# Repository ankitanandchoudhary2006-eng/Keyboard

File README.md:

# Keyboard

I made a custom 60% layout keyboard which has per swich diode for ghosting protection and it has hotswaps So that we can change the switches anytime as per our wich . The MCU is based on STM32F072CBT6 and we have designed the circuit using  a custom chip to save space (instread of a module). PCB was designed in Kicad and CAD was made in Fusion.

### Features
- Based on STM32F072CBT6 Chip
- Has 60% Compact layout
- uses diodes for ghosting prevention

# BOM - Bill of Materials

## Components

| Component | Qty | Total Price (USD) | Purchase Link |
|---|---:|---:|---|
| 4.7uF Capacitor | 2 | $0.226 | [JLCPCB](https://jlcpcb.com/partdetail/24469-CL05A475MP5NRNC/C23733) |
| 100nF Capacitor | 4 | $0.0552 | [JLCPCB](https://jlcpcb.com/partdetail/1877-CL05B104KO5NNNC/C1525) |
| 1uF Capacitor | 4 | $0.110 | [JLCPCB](https://jlcpcb.com/partdetail/53938-CL05A105KA5NQNC/C52923) |
| 10uF Capacitor | 1 | $0.394 | [JLCPCB](https://jlcpcb.com/partdetail/16204-CL05A106MQ5NUNC/C15525) |
| PRTR5V0U2X | 1 | $0.3762 | [JLCPCB](https://jlcpcb.com/partdetail/TECHPUBLIC-PRTR5V0U2X/C2827688) |
| 1N4148W Diode | 60 | $1.6616 | [JLCPCB](https://jlcpcb.com/partdetail/ST_Semtech-1N4148W/C81598) |
| 500mA Fuse | 1 | $0.2538 | [JLCPCB](https://jlcpcb.com/partdetail/TECHFUSE-nSMD050/C69688) |
| 2N7002 MOSFET | 1 | $0.158 | [JLCPCB](https://jlcpcb.com/partdetail/9040-2N7002/C8545) |
| 5.1k Resistor | 2 | $0.028 | [JLCPCB](https://jlcpcb.com/partdetail/26648-0402WGF5101TCE/C25905) |
| 33k Resistor | 1 | $0.038 | [JLCPCB](https://jlcpcb.com/partdetail/26522-0402WGF3302TCE/C25779) |
| 10k Resistor | 1 | $0.030 | [JLCPCB](https://jlcpcb.com/partdetail/26487-0402WGF1002TCE/C25744) |
| 100k Resistor | 1 | $0.018 | [JLCPCB](https://jlcpcb.com/partdetail/26484-0402WGF1003TCE/C25741) |
| Tactile Switch | 1 | $0.215 | [JLCPCB](https://jlcpcb.com/partdetail/XKBConnection-TS_1187A_B_AB/C318884) |
| XC6206P332MR | 1 | $0.690 | [JLCPCB](https://jlcpcb.com/partdetail/TorexSemicon-XC6206P332MRG/C5446) |
| STM32F072CBT6 | 1 | $5.518 | [JLCPCB](https://jlcpcb.com/partdetail/STMicroelectronics-STM32F072C8T6/C80488) |
| USB Type-C Connector | 1 | $0.3738 | [JLCPCB](https://jlcpcb.com/partdetail/Korean_HropartsElec-TYPE_C_31_M12/C165948) |
| HOTSWAP Socket | 61 | $0.00 (Already Have) | [Meckeys](https://meckeys.com/shop/accessories/keyboard-accessories/key-switches/kailh-hot-swap-socket/?attribute_pa_variations=white) |
|Stabalizers |1|0|https://meckeys.com/shop/accessories/keyboard-accessories/more/glorious-goat-stabilizers/|

## Manufacturing Cost

| Item | Price (USD) |
|---|---:|
| PCB Engineering Fee | $4.00 |
| PCB Board | $14.70 |
| Via Covering | $0.00 |
| **PCB Total** | **$18.70** |
| PCBA Setup Fee | $25.75 |
| Stencil | $8.27 |
| Components | $10.15 |
| Feeder Loading Fee | $24.80 |
| SMT Assembly | $1.43 |
| Packaging Fee | $0.51 |
| **PCBA Total** | **$70.91** |

## Additional Costs

| Item | Price (USD) |
|---|---:|
| 3D Printing | $11.29 |
| Shipping | $18.24 |

## Final Project Cost

| Category | Price (USD) |
|---|---:|
| PCB Fabrication | $18.70 |
| PCBA Assembly | $70.91 |
| 3D Printing | $11.29 |
| Shipping | $18.24 |
| **Grand Total** | **$119.14** |

**Total Project Cost: $119.14 USD**

## Schematics

## PCB

## CAD

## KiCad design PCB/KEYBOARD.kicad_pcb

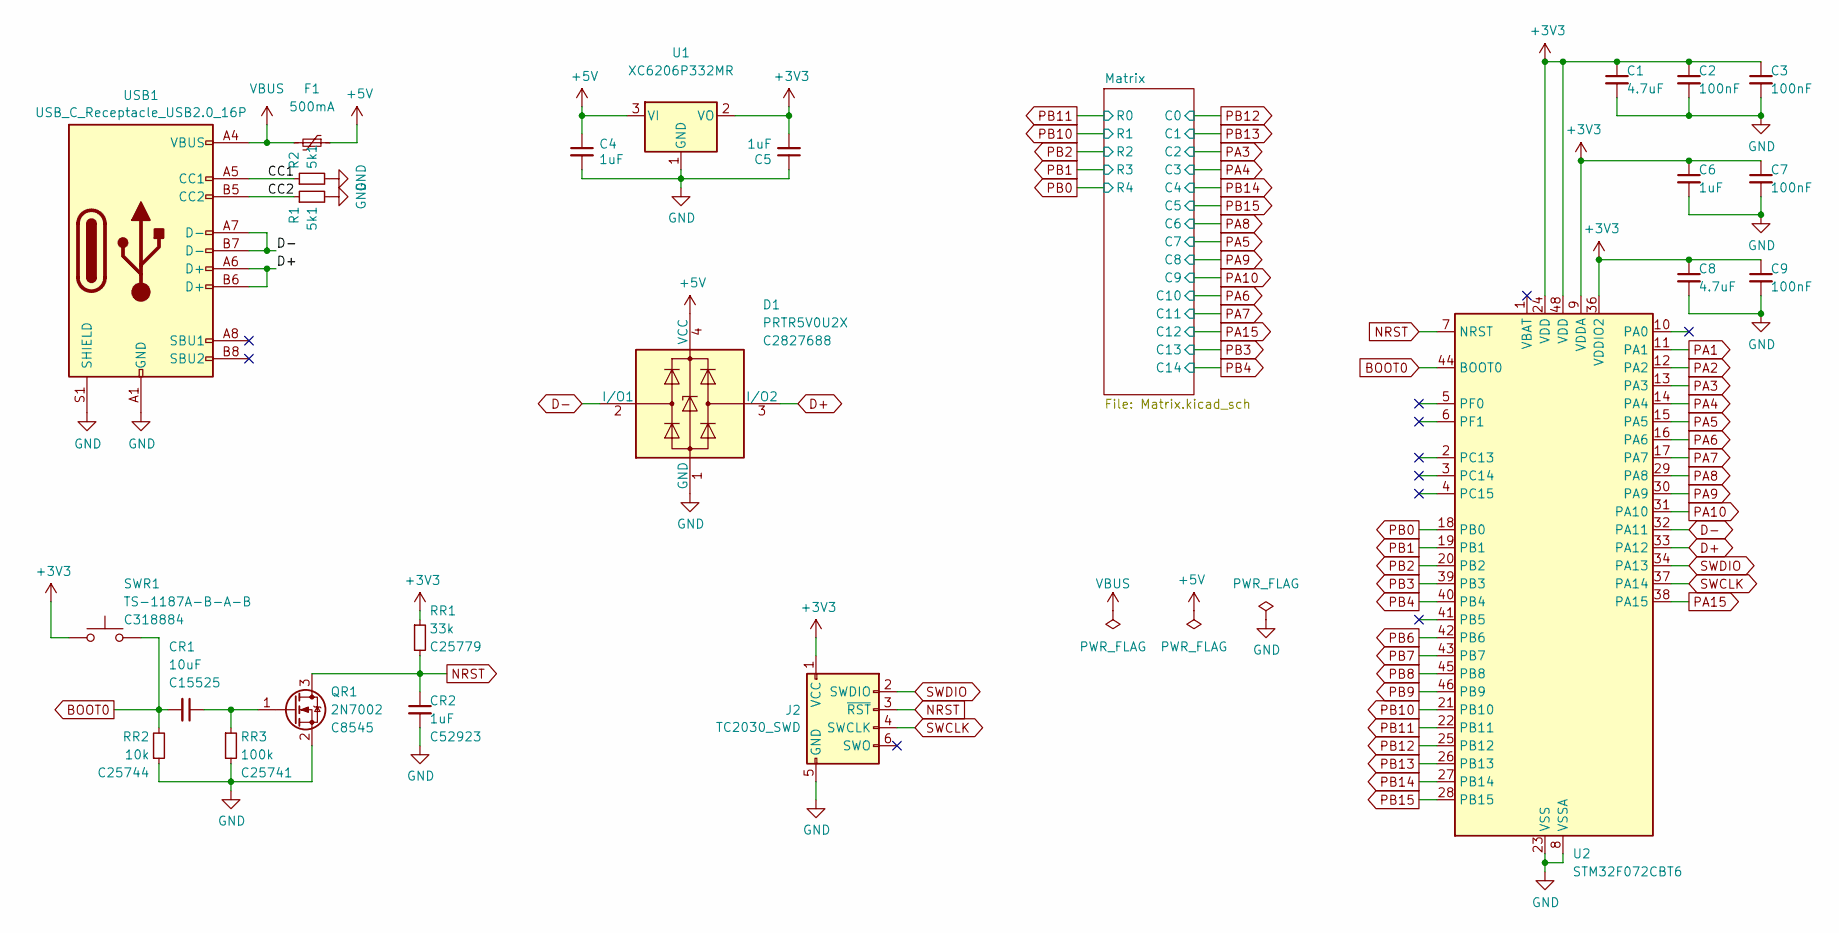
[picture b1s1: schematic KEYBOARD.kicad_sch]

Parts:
C1, C8: 4.7uF; C_0402_1005Metric; MPN CL05A475MP5NRNC; LCSC C23733
C2, C3, C7, C9: 100nF; C_0402_1005Metric; MPN CL05B104KO5NNNC; LCSC C1525
C4, C5, C6: 1uF; C_0402_1005Metric; MPN CL05A105KA5NQNC; LCSC C52923
CR1: 10uF; C_0402_1005Metric; MPN CL05A106MQ5NUNC; LCSC C15525
CR2: 1uF; C_0402_1005Metric; MPN CL05A105KA5NQNC; LCSC C52923
D1: PRTR5V0U2X; SOT-143; MPN PRTR5V0U2X; LCSC C2827688
F1: 500mA; Fuse_1206_3216Metric_Pad1.42x1.75mm_HandSolder; MPN nSMD050; LCSC C69688
J2: TC2030_SWD; CON_TC2030_outlined
QR1: 2N7002; SOT-23; MPN 2N7002; LCSC C8545
R1, R2: 5k1; R_0402_1005Metric; MPN 0402WGF5101TCE; LCSC C25905
RR1: 33k; R_0402_1005Metric; MPN 0402WGF3302TCE; LCSC C25779
RR2: 10k; R_0402_1005Metric; MPN 0402WGF1002TCE; LCSC C25744
RR3: 100k; R_0402_1005Metric; MPN 0402WGF1003TCE; LCSC C25741
SWR1: TS-1187A-B-A-B; SW_SPST_TL3342; MPN TS-1187A-B-A-B; LCSC C318884
U1: XC6206P332MR; SOT-23; MPN XC6206P332MR-G; LCSC C5446
U2: STM32F072CBT6; LQFP-48_7x7mm_P0.5mm; MPN STM32F072CBT6; LCSC C81720
USB1: USB_C_Receptacle_USB2.0_16P; USB_C_Receptacle_HRO_TYPE-C-31-M-12; MPN TYPE-C-31-M-12; LCSC C165948

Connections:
+3V3: C1.1, C2.1, C3.1, C5.2, C6.1, C7.1, C8.1, C9.1, J2.1 (VCC), RR1.1, SWR1.1, U1.2 (VO), U2.9 (VDDA), U2.24 (VDD), U2.36 (VDDIO2), U2.48 (VDD)
+5V: C4.1, D1.4 (VCC), F1.1, U1.3 (VI)
/CC1: R2.1, USB1.A5 (CC1)
/CC2: R1.1, USB1.B5 (CC2)
BOOT0: CR1.2, RR2.2, SWR1.2, U2.44 (BOOT0)
D+: D1.3 (I/O2), U2.33 (PA12), USB1.A6 (D+), USB1.B6 (D+)
D-: D1.2 (I/O1), U2.32 (PA11), USB1.A7 (D-), USB1.B7 (D-)
GND: C1.2, C2.2, C3.2, C4.2, C5.1, C6.2, C7.2, C8.2, C9.2, CR2.2, D1.1 (GND), J2.5 (GND), QR1.2 (S), R1.2, R2.2, RR2.1, RR3.2, U1.1 (GND), U2.8 (VSSA), U2.23 (VSS), U2.35 (VSS), U2.47 (VSS), USB1.A1 (GND), USB1.A12 (GND), USB1.B1 (GND), USB1.B12 (GND), USB1.S1 (SHIELD)
NRST: CR2.1, J2.3 (~RST), QR1.3 (D), RR1.2, U2.7 (NRST)
unnamed: CR1.1, QR1.1 (G), RR3.1
PA1: U2.11 (PA1)
PA2: U2.12 (PA2)
PA3: U2.13 (PA3); also elsewhere on the board
PA4: U2.14 (PA4); also elsewhere on the board
PA5: U2.15 (PA5); also elsewhere on the board
PA6: U2.16 (PA6); also elsewhere on the board
PA7: U2.17 (PA7); also elsewhere on the board
PA8: U2.29 (PA8); also elsewhere on the board
PA9: U2.30 (PA9); also elsewhere on the board
PA10: U2.31 (PA10); also elsewhere on the board
PA15: U2.38 (PA15); also elsewhere on the board
PB0: U2.18 (PB0); also elsewhere on the board
PB1: U2.19 (PB1); also elsewhere on the board
PB2: U2.20 (PB2); also elsewhere on the board
PB3: U2.39 (PB3); also elsewhere on the board
PB4: U2.40 (PB4); also elsewhere on the board
PB6: U2.42 (PB6)
PB7: U2.43 (PB7)
PB8: U2.45 (PB8)
PB9: U2.46 (PB9)
PB10: U2.21 (PB10); also elsewhere on the board
PB11: U2.22 (PB11); also elsewhere on the board
PB12: U2.25 (PB12); also elsewhere on the board
PB13: U2.26 (PB13); also elsewhere on the board
PB14: U2.27 (PB14); also elsewhere on the board
PB15: U2.28 (PB15); also elsewhere on the board
SWCLK: J2.4 (SWCLK), U2.37 (PA14)
SWDIO: J2.2 (SWDIO), U2.34 (PA13)
VBUS: F1.2, USB1.A4 (VBUS), USB1.A9 (VBUS), USB1.B4 (VBUS), USB1.B9 (VBUS)

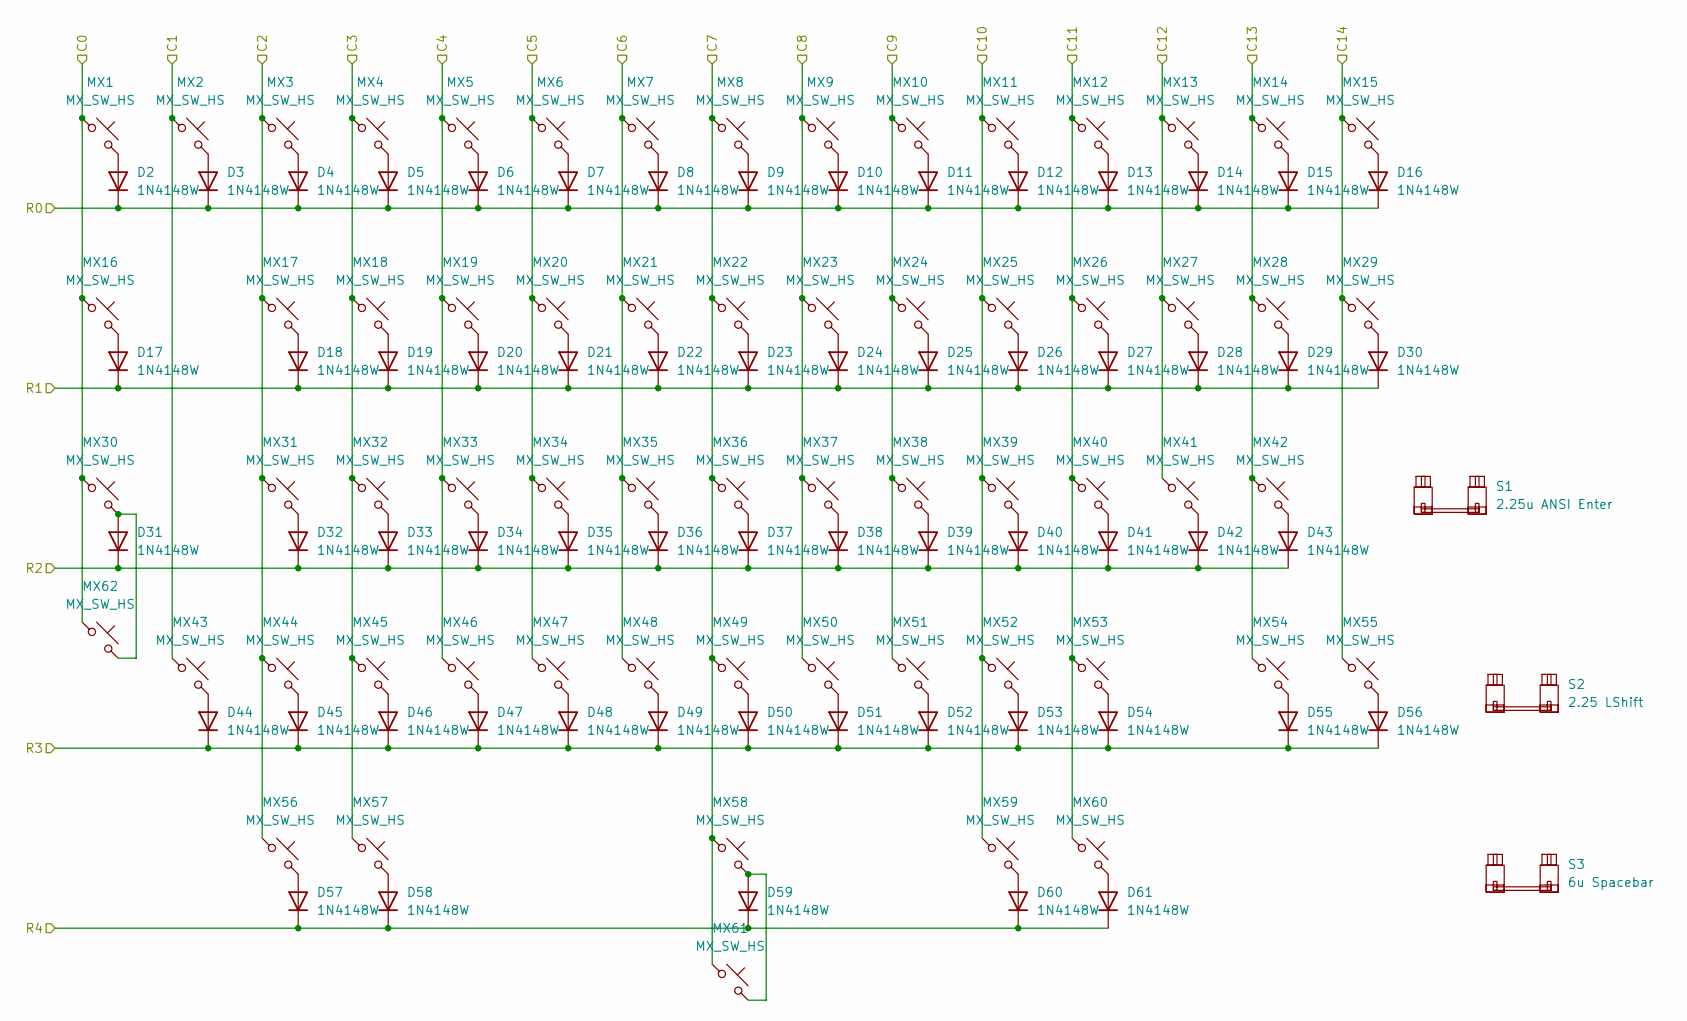
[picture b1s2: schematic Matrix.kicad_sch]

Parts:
D2, D3, D4, D5, D6, D7, D8, D9, D10, D11, D12, D13, D14, D15, D16, D17, D18, D19, D20, D21, D22, D23, D24, D25, D26, D27, D28, D29, D30, D31, D32, D33, D34, D35, D36, D37, D38, D39, D40, D41, D42, D43, D44, D45, D46, D47, D48, D49, D50, D51, D52, D53, D54, D55, D56, D57, D58, D59, D60, D61: 1N4148W; D_SOD-123
MX1, MX2, MX3, MX4, MX5, MX6, MX7, MX8, MX9, MX10, MX11, MX12, MX13, MX14, MX15, MX17, MX18, MX19, MX20, MX21, MX22, MX23, MX24, MX25, MX26, MX27, MX28, MX31, MX32, MX33, MX34, MX35, MX36, MX37, MX38, MX39, MX40, MX41, MX42, MX43, MX44, MX45, MX46, MX47, MX48, MX49, MX50, MX51, MX52, MX53, MX55, MX56, MX58, MX60, MX61: MX_SW_HS; SW_MX_HS_CPG151101S11_1u
MX16, MX29, MX57, MX59: MX_SW_HS; SW_MX_HS_CPG151101S11_1.5u
MX30, MX54: MX_SW_HS; SW_MX_HS_CPG151101S11_1.75u
MX62: MX_SW_HS; SW_MX_HS_CPG151101S11_1.75u_STP_1.25
S1: 2.25u ANSI Enter; STAB_MX_2.25u
S2: 2.25 LShift; STAB_MX_2.25u
S3: 6u Spacebar; STAB_MX_6u_New

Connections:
unnamed: D2.2 (A), MX1.2
unnamed: D3.2 (A), MX2.2
unnamed: D4.2 (A), MX3.2
unnamed: D5.2 (A), MX4.2
unnamed: D6.2 (A), MX5.2
unnamed: D7.2 (A), MX6.2
unnamed: D8.2 (A), MX7.2
unnamed: D9.2 (A), MX8.2
unnamed: D10.2 (A), MX9.2
unnamed: D11.2 (A), MX10.2
unnamed: D12.2 (A), MX11.2
unnamed: D13.2 (A), MX12.2
unnamed: D14.2 (A), MX13.2
unnamed: D15.2 (A), MX14.2
unnamed: D16.2 (A), MX15.2
unnamed: D17.2 (A), MX16.2
unnamed: D18.2 (A), MX17.2
unnamed: D19.2 (A), MX18.2
unnamed: D20.2 (A), MX19.2
unnamed: D21.2 (A), MX20.2
unnamed: D22.2 (A), MX21.2
unnamed: D23.2 (A), MX22.2
unnamed: D24.2 (A), MX23.2
unnamed: D25.2 (A), MX24.2
unnamed: D26.2 (A), MX25.2
unnamed: D27.2 (A), MX26.2
unnamed: D28.2 (A), MX27.2
unnamed: D29.2 (A), MX28.2
unnamed: D30.2 (A), MX29.2
unnamed: D31.2 (A), MX30.2, MX62.2
unnamed: D32.2 (A), MX31.2
unnamed: D33.2 (A), MX32.2
unnamed: D34.2 (A), MX33.2
unnamed: D35.2 (A), MX34.2
unnamed: D36.2 (A), MX35.2
unnamed: D37.2 (A), MX36.2
unnamed: D38.2 (A), MX37.2
unnamed: D39.2 (A), MX38.2
unnamed: D40.2 (A), MX39.2
unnamed: D41.2 (A), MX40.2
unnamed: D42.2 (A), MX41.2
unnamed: D43.2 (A), MX42.2
unnamed: D44.2 (A), MX43.2
unnamed: D45.2 (A), MX44.2
unnamed: D46.2 (A), MX45.2
unnamed: D47.2 (A), MX46.2
unnamed: D48.2 (A), MX47.2
unnamed: D49.2 (A), MX48.2
unnamed: D50.2 (A), MX49.2
unnamed: D51.2 (A), MX50.2
unnamed: D52.2 (A), MX51.2
unnamed: D53.2 (A), MX52.2
unnamed: D54.2 (A), MX53.2
unnamed: D55.2 (A), MX54.2
unnamed: D56.2 (A), MX55.2
unnamed: D57.2 (A), MX56.2
unnamed: D58.2 (A), MX57.2
unnamed: D59.2 (A), MX58.2, MX61.2
unnamed: D60.2 (A), MX59.2
unnamed: D61.2 (A), MX60.2
PA3: MX3.1, MX17.1, MX31.1, MX44.1, MX56.1; also elsewhere on the board
PA4: MX4.1, MX18.1, MX32.1, MX45.1, MX57.1; also elsewhere on the board
PA5: MX8.1, MX22.1, MX36.1, MX49.1, MX58.1, MX61.1; also elsewhere on the board
PA6: MX11.1, MX25.1, MX39.1, MX52.1, MX59.1; also elsewhere on the board
PA7: MX12.1, MX26.1, MX40.1, MX53.1, MX60.1; also elsewhere on the board
PA8: MX7.1, MX21.1, MX35.1, MX48.1; also elsewhere on the board
PA9: MX9.1, MX23.1, MX37.1, MX50.1; also elsewhere on the board
PA10: MX10.1, MX24.1, MX38.1, MX51.1; also elsewhere on the board
PA15: MX13.1, MX27.1, MX41.1; also elsewhere on the board
PB0: D57.1 (K), D58.1 (K), D59.1 (K), D60.1 (K), D61.1 (K); also elsewhere on the board
PB1: D44.1 (K), D45.1 (K), D46.1 (K), D47.1 (K), D48.1 (K), D49.1 (K), D50.1 (K), D51.1 (K), D52.1 (K), D53.1 (K), D54.1 (K), D55.1 (K), D56.1 (K); also elsewhere on the board
PB2: D31.1 (K), D32.1 (K), D33.1 (K), D34.1 (K), D35.1 (K), D36.1 (K), D37.1 (K), D38.1 (K), D39.1 (K), D40.1 (K), D41.1 (K), D42.1 (K), D43.1 (K); also elsewhere on the board
PB3: MX14.1, MX28.1, MX42.1, MX54.1; also elsewhere on the board
PB4: MX15.1, MX29.1, MX55.1; also elsewhere on the board
PB10: D17.1 (K), D18.1 (K), D19.1 (K), D20.1 (K), D21.1 (K), D22.1 (K), D23.1 (K), D24.1 (K), D25.1 (K), D26.1 (K), D27.1 (K), D28.1 (K), D29.1 (K), D30.1 (K); also elsewhere on the board
PB11: D2.1 (K), D3.1 (K), D4.1 (K), D5.1 (K), D6.1 (K), D7.1 (K), D8.1 (K), D9.1 (K), D10.1 (K), D11.1 (K), D12.1 (K), D13.1 (K), D14.1 (K), D15.1 (K), D16.1 (K); also elsewhere on the board
PB12: MX1.1, MX16.1, MX30.1, MX62.1; also elsewhere on the board
PB13: MX2.1, MX43.1; also elsewhere on the board
PB14: MX5.1, MX19.1, MX33.1, MX46.1; also elsewhere on the board
PB15: MX6.1, MX20.1, MX34.1, MX47.1; also elsewhere on the board

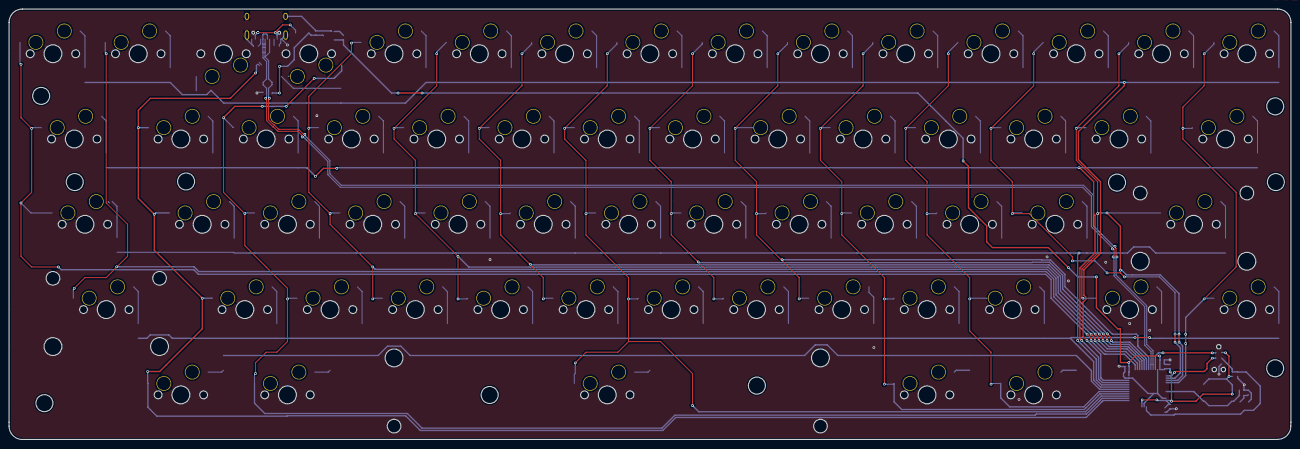
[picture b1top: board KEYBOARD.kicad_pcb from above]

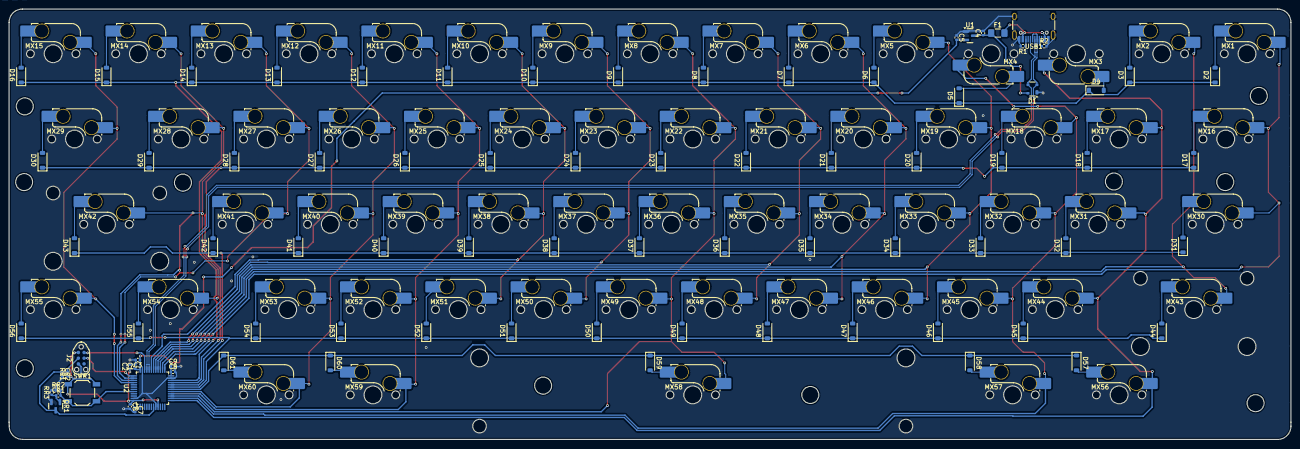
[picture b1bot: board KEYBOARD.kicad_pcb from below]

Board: 2 copper layers, 286.4 x 96.1 mm, 147 parts (144 on the bottom side), 93 nets.

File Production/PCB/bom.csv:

Designator,Footprint,Quantity,Value,LCSC Part #
"C1, C8",0402,2,4.7uF,C23733
"C2, C3, C7, C9",0402,4,100nF,C1525
"C4, C5, C6, CR2",0402,4,1uF,C52923
CR1,0402,1,10uF,C15525
D1,SOT-143,1,PRTR5V0U2X,C2827688
"D10, D11, D12, D13, D14, D15, D16, D17, D18, D19, D2, D20, D21, D22, D23, D24, D25, D26, D27, D28, D29, D3, D30, D31, D32, D33, D34, D35, D36, D37, D38, D39, D4, D40, D41, D42, D43, D44, D45, D46, D47, D48, D49, D5, D50, D51, D52, D53, D54, D55, D56, D57, D58, D59, D6, D60, D61, D7, D8, D9",D_SOD-123,60,1N4148W,
F1,1206,1,500mA,C69688
"MX1, MX10, MX11, MX12, MX13, MX14, MX15, MX17, MX18, MX19, MX2, MX20, MX21, MX22, MX23, MX24, MX25, MX26, MX27, MX28, MX3, MX31, MX32, MX33, MX34, MX35, MX36, MX37, MX38, MX39, MX4, MX40, MX41, MX42, MX43, MX44, MX45, MX46, MX47, MX48, MX49, MX5, MX50, MX51, MX52, MX53, MX55, MX56, MX58, MX6, MX60, MX7, MX8, MX9",SW_MX_HS_CPG151101S11_1u,54,MX_SW_HS,
"MX16, MX29, MX57, MX59",SW_MX_HS_CPG151101S11_1.5u,4,MX_SW_HS,
"MX30, MX54",SW_MX_HS_CPG151101S11_1.75u,2,MX_SW_HS,
QR1,SOT-23,1,2N7002,C8545
"R1, R2",0402,2,5k1,C25905
RR1,0402,1,33k,C25779
RR2,0402,1,10k,C25744
RR3,0402,1,100k,C25741
SWR1,SW_SPST_TL3342,1,TS-1187A-B-A-B,C318884
U1,SOT-23,1,XC6206P332MR,C5446
U2,LQFP-48_7x7mm_P0.5mm,1,STM32F072CBT6,C81720
USB1,USB_C_Receptacle_HRO_TYPE-C-31-M-12,1,USB_C_Receptacle_USB2.0_16P,C165948
